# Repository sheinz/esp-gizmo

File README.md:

# esp-gizmo
Experiments with esp8266

# Wall switch variant

## TODO

### Features

First priority:
 * Operate like a normal wall switch.
 * Receive commands via MQTT and turn on/off lights.

Second priority:
 * Report status (switch position).
 * OTA firmware update.
 * Quick configuration.

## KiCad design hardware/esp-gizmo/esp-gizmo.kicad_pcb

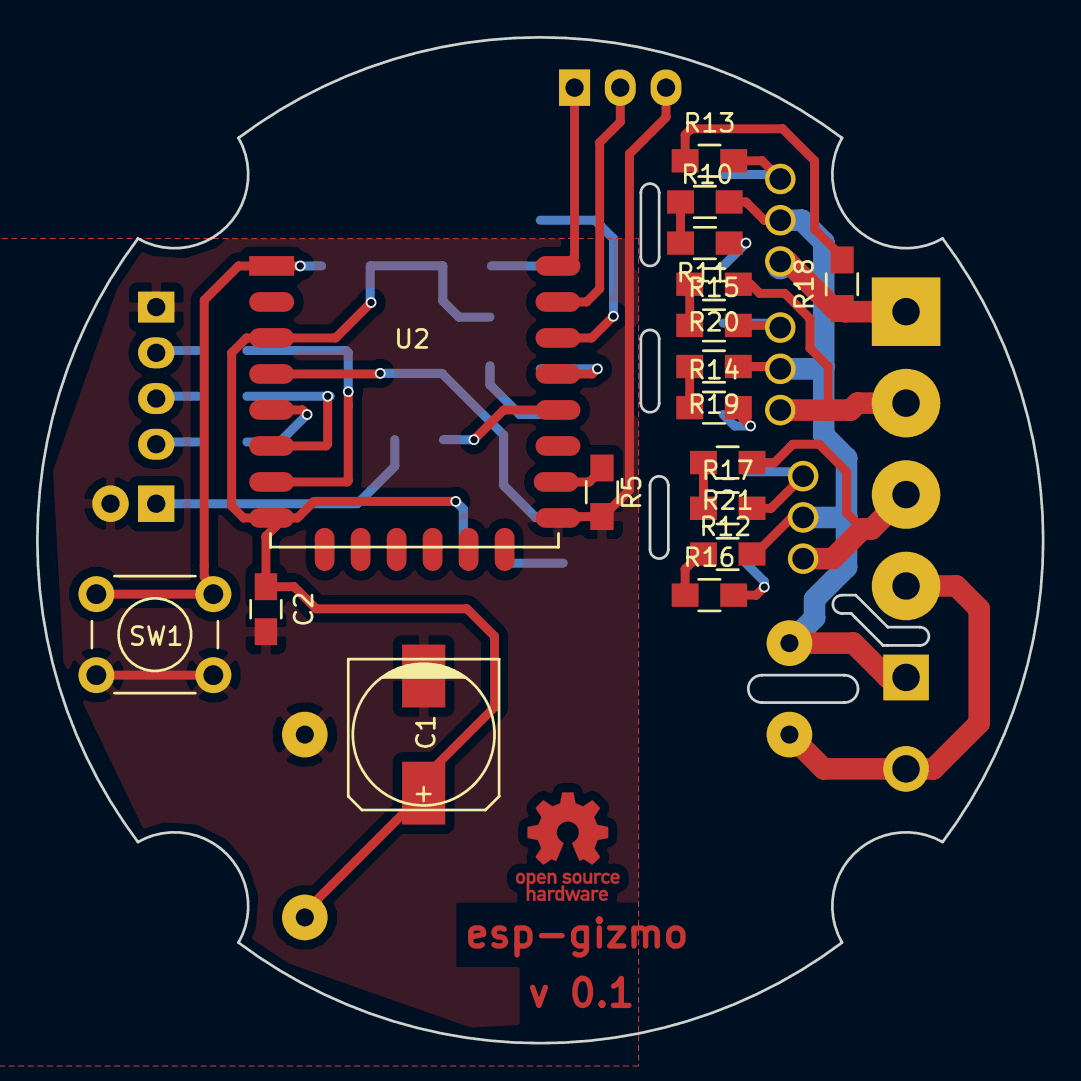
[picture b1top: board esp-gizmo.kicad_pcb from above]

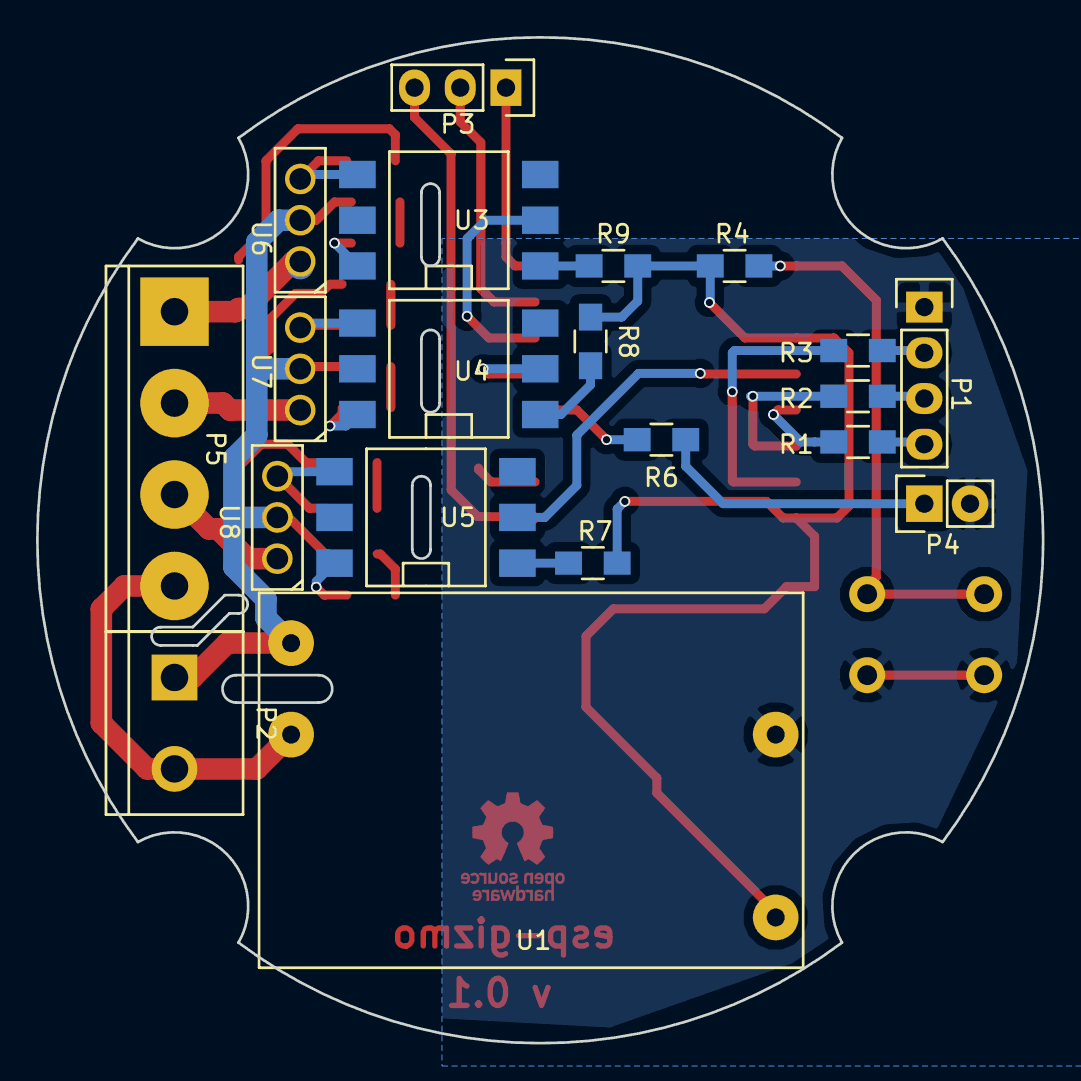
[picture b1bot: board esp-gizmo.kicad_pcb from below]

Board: 2 copper layers, 55.9 x 55.9 mm, 37 parts (20 on the bottom side), 37 nets.

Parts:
C1: 1000u; c_elec_8x10
C2: 100n; C_0805_HandSoldering
P1: CONN_01X04; Pin_Header_Straight_1x04
P2: CONN_01X02; bornier2
P3: CONN_01X03; Pin_Header_Straight_1x03
P4: BOOT JUMPER; Pin_Header_Straight_1x02
P5: CONN_01X04; bornier4
R1, R2, R3, R5, R6: 1k; R_0805_HandSoldering
R4: 10k; R_0805_HandSoldering
R7, R8, R9: 430; R_0805_HandSoldering
R10, R11, R12, R13, R14, R15, R16, R17, R18, R19, R20, R21: 160; R_0805_HandSoldering
SW1: SPST; SW_PUSH_6mm
U1: AC-DC; AC_DC
U2: ESP-12E
U3, U4, U5: MOC3063; DIP-6_SMD
U6, U7, U8: TRIAC; SOT126_SOT32_Housing_Vertical

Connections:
+3V3: C1.1, C2.1, R4.1, R7.1, R8.1, R9.1, U1.3, U2.3, U2.8
/COMMON: P2.2, P5.4, U1.2
/LOAD1: P5.1, R18.1, U6.1
/LOAD2: P5.2, R20.1, U7.1
/LOAD3: P5.3, R21.1, U8.1
GND: C1.2, C2.2, P1.1, P3.3, P4.2, R5.2, SW1.1, U1.4, U2.15
unnamed: P1.2, R3.2
unnamed: P1.3, R2.2
unnamed: P1.4, R1.2
unnamed: P2.1, R10.1, R12.1, R19.1, U1.1, U6.2, U7.2, U8.2
unnamed: P3.1, U2.22
unnamed: P3.2, U2.21
unnamed: P4.1, R6.1
unnamed: R1.1, U2.5
unnamed: R2.1, U2.6
unnamed: R3.1, U2.7
unnamed: R4.2, SW1.2, U2.1
unnamed: R5.1, U2.16
unnamed: R6.2, U2.18
unnamed: R7.2, U5.1
unnamed: R8.2, U4.1
unnamed: R9.2, U3.1
unnamed: R10.2, R11.1
unnamed: R11.2, U3.6
unnamed: R12.2, R16.1
unnamed: R13.1, R18.2
unnamed: R13.2, U3.4, U6.3
unnamed: R14.1, R19.2
unnamed: R14.2, U4.6
unnamed: R15.1, R20.2
unnamed: R15.2, U4.4, U7.3
unnamed: R16.2, U5.6
unnamed: R17.1, R21.2
unnamed: R17.2, U5.4, U8.3
unnamed: U2.4, U5.2
unnamed: U2.19, U4.2
unnamed: U2.20, U3.2

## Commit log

2016-04-02 Initial commit. Ota update sample.
2016-04-02 Switched to Swing. Initial version of OTA update.
2016-04-20 Draft cmake project with mqtt library
2016-04-20 Removed .ropeproject directory
2016-05-04 Lamp pin changed
2016-08-05 Simple thingspeak example
2016-08-26 Add draft schematic
2016-08-26 Draft pcb design
2016-08-26 Some fixes of schematic and board
2016-10-14 Different build variants
2016-10-14 Initial switch variant implementation
2016-10-14 Switch: Add load control
2016-10-16 OTA update
2016-10-16 Draft mqtt task
2016-10-19 Tweaked tasks priority and mqtt data polling
2016-10-19 Reporting switches status
2016-11-06 Add DS18B20 temperature sensor. Update FreeRTOS types
2016-11-09 Schematic: switch to zero crossing opto-coupler
